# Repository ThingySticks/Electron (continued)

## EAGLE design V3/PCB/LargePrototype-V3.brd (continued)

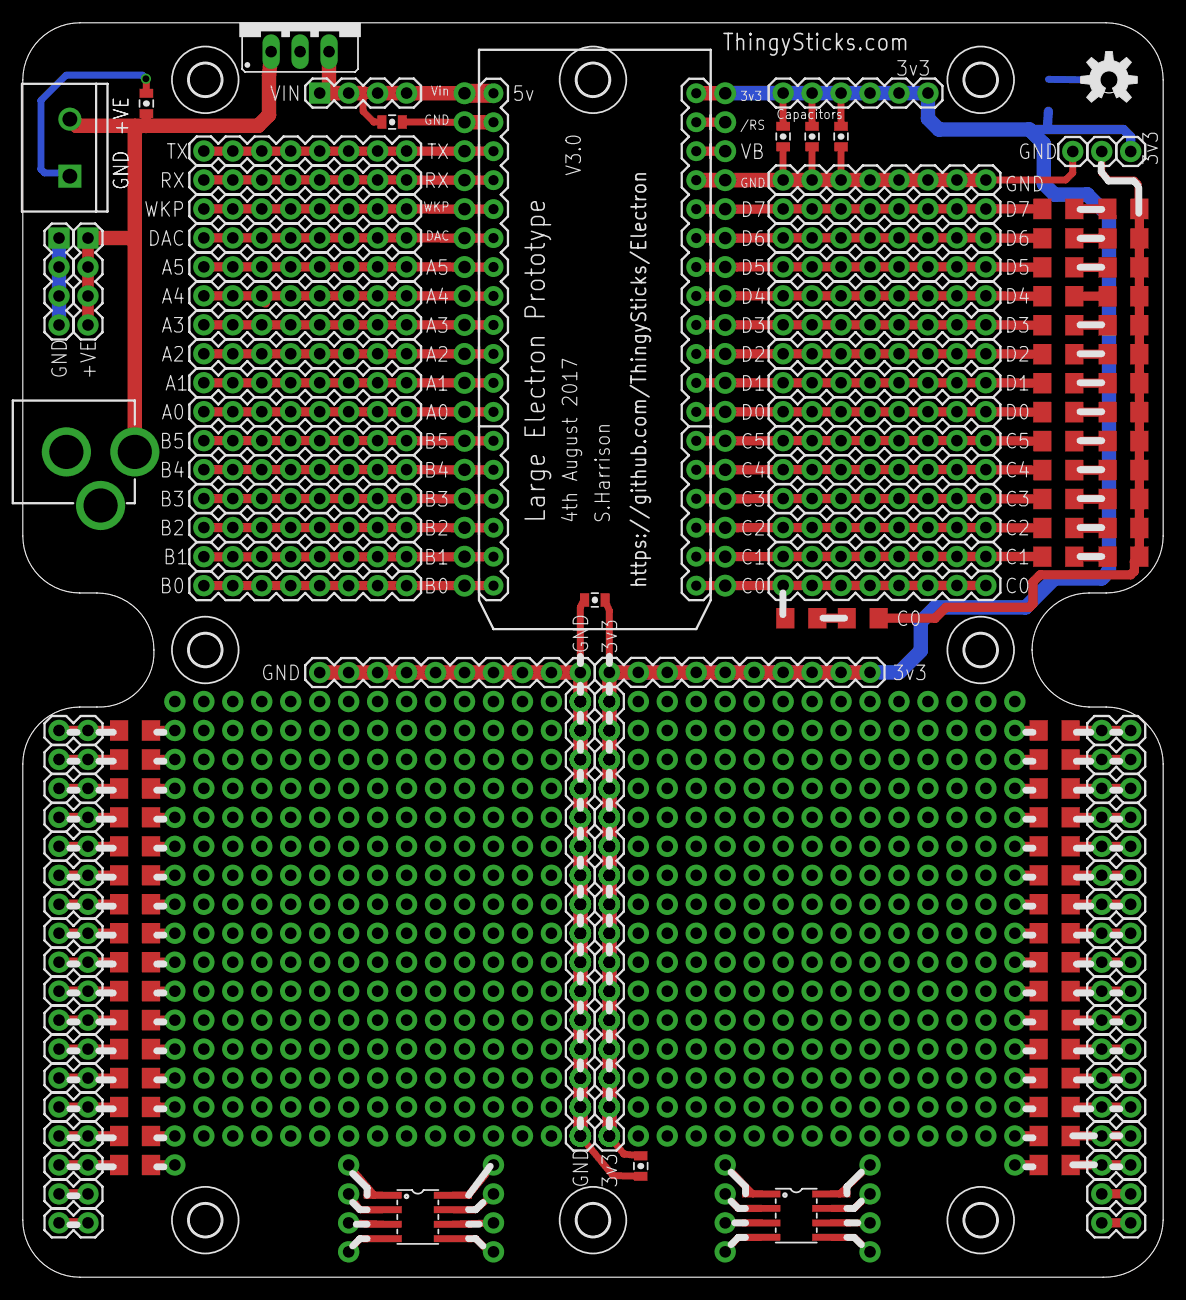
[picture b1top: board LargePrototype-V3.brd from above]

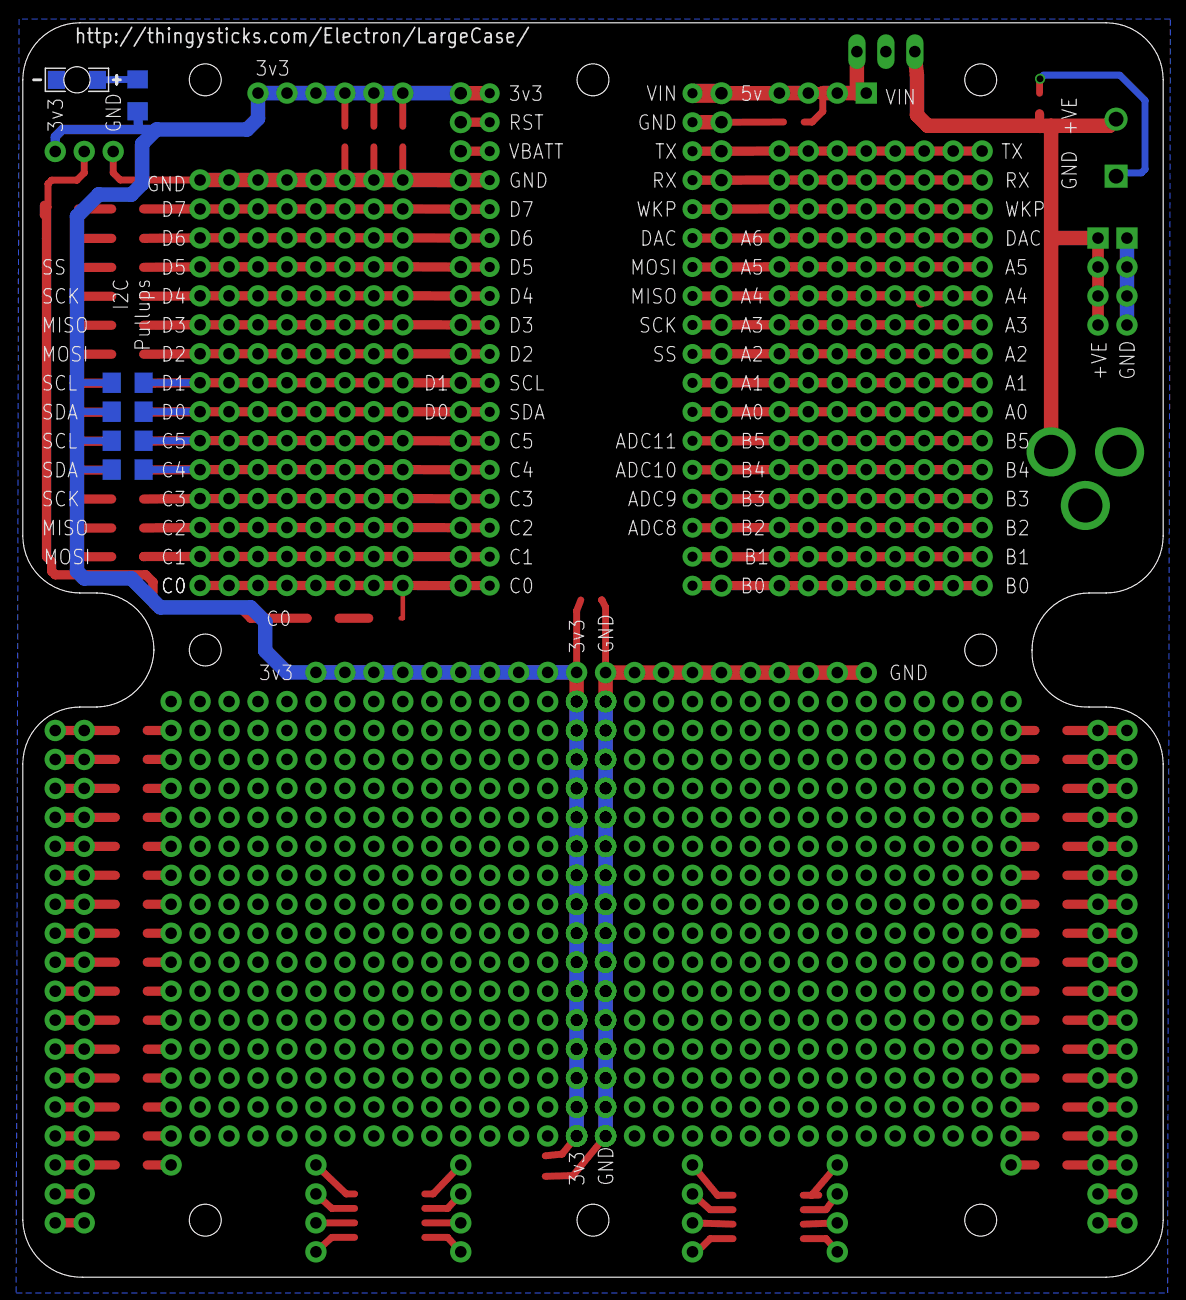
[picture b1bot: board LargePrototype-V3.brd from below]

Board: 2 copper layers, 100.0 x 110.0 mm, 205 parts (6 on the bottom side), 136 nets.

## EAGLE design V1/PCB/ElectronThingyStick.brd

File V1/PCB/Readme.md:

Electron Prototyping PCB.
=========================

Prototype board for Particle Electron.

Features:
---------

* USB power in via A Connector on left edge or B Connector on Electron. (Do not connect both at once).
* Pull-up and down 1206 pads on A0-A7 and B0-B7. Suitable for 1206 or 0805 components.
* LED/Resistor/Capacitor 1206 pads Right edge along with 10 x 2 header for off board connection (8 pins to 1206's + 2v2 & GND).
* 4 1206 pads top/bottom by end of Photon connected to pins to the right of the pad. Ideal of Capacitors, Resistor or LED.
* 3 Mounting holes to allow board to be mounted in case for final use.
* SOT-23 FET/Transistor under Photon with Gate/Base 1206 guard and pull down resistor options.

Mounting:
---------

Single hole middle PCB (at 14.5, 22)
Double holes end PCB (at 96,4 & 96,40)

Size:
-----
Length: 100mm
Width: 44mm

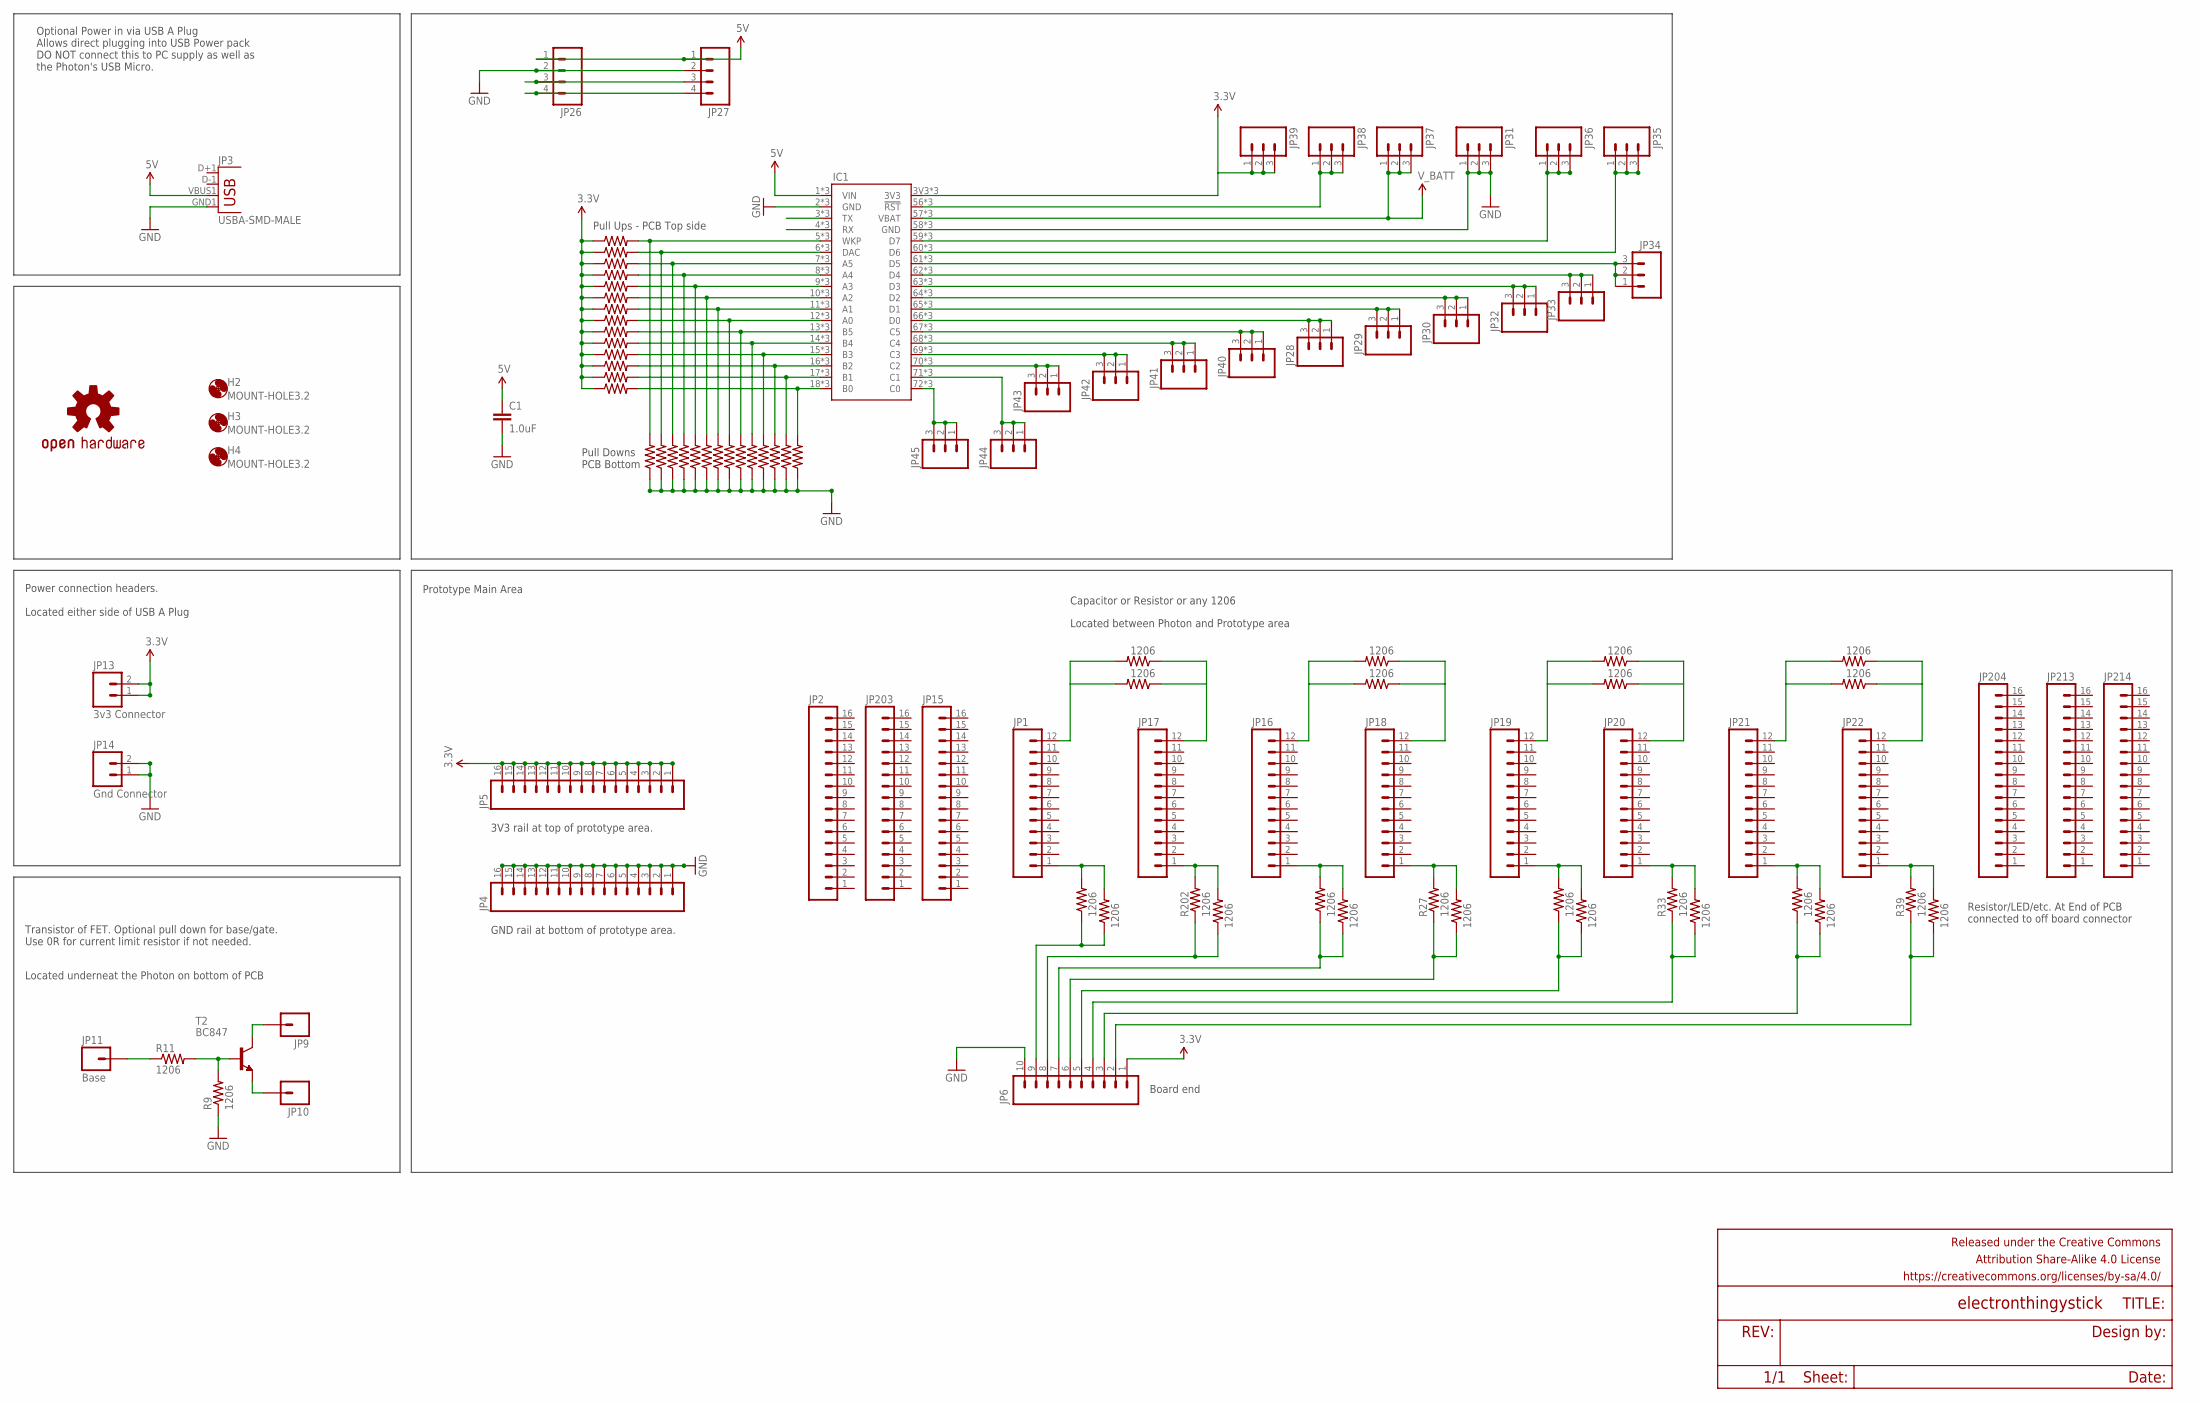
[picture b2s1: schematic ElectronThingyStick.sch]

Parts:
C1: 1.0uF; 0805-CAP
FRAME1: FRAME-LEDGER; CREATIVE_COMMONS
H2, H3, H4: MOUNT-HOLE3.2; 3,2
IC1: ELECTRONDUALROW; ELECTRON_DUAL-ROW
JP1, JP16, JP17, JP18, JP19, JP20, JP21, JP22: M12NO_SILK; 1X12_NO_SILK
JP2, JP15, JP203, JP204, JP213, JP214: M161X16_NO_SILK; 1X16_NO_SILK
JP3: USBA-SMD-MALE; USB-A-SMT-MALE
JP4, JP5: M16PTH; 1X16
JP6: M10NO_SILK_PTH_FEMALE; 1X10_NO_SILK
JP9, JP10: M01PTH; 1X01
JP11: Base; 1X01
JP13: 3v3 Connector; 1X02
JP14: Gnd Connector; 1X02
JP26, JP27: M041X04_NO_SILK; 1X04_NO_SILK
JP28, JP29, JP30, JP31, JP32, JP33, JP34, JP35, JP36, JP37, JP38, JP39, JP40, JP41, JP42, JP43, JP44, JP45: M03PTH; 1X03
LOGO1: OSHW-LOGOM; OSHW-LOGO-M
R1, R2, R3, R4, R5, R6, R7, R8, R9, R10, R11, R12, R13, R14, R15, R16, R17, R18, R19, R20, R21, R22, R23, R24, R25, R26, R27, R28, R29, R30, R31, R32, R33, R34, R35, R36, R37, R38, R39, R40, R41, R42, R43, R44, R45, R46, R47, R48, R49, R50, R51, R52, R201, R202: 1206
T2: BC847; SOT23

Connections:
3.3V: IC1.3V3, IC1.55 (3V3), IC1.91 (3V3), JP5.1, JP5.2, JP5.3, JP5.4, JP5.5, JP5.6, JP5.7, JP5.8, JP5.9, JP5.10, JP5.11, JP5.12, JP5.13, JP5.14, JP5.15, JP5.16, JP6.1, JP13.1, JP13.2, JP39.1, JP39.2, JP39.3, R1.1, R2.1, R3.1, R4.1, R5.1, R6.1, R7.1, R12.1, R15.1, R16.1, R17.1, R18.1, R45.1, R46.1
5V: C1.1, IC1.1 (VIN), IC1.37 (VIN), IC1.VIN, JP3.VBUS1 (VBUS), JP26.1, JP27.1
GND: C1.2, IC1.2 (GND), IC1.38 (GND), IC1.58 (GND), IC1.94 (GND), IC1.GND, IC1.GND@2 (GND), JP3.GND1 (GND), JP4.1, JP4.2, JP4.3, JP4.4, JP4.5, JP4.6, JP4.7, JP4.8, JP4.9, JP4.10, JP4.11, JP4.12, JP4.13, JP4.14, JP4.15, JP4.16, JP6.10, JP14.1, JP14.2, JP26.2, JP27.2, JP31.1, JP31.2, JP31.3, R8.1, R9.1, R10.1, R13.1, R14.1, R19.1, R20.1, R21.1, R22.1, R47.1, R48.1, R49.1, R50.1, R51.1, R52.1
unnamed: IC1.67 (C5), IC1.103 (C5), IC1.C5, JP40.1, JP40.2, JP40.3
unnamed: JP17.1, R26.2, R202.2
unnamed: JP1.1, R23.2, R201.2
unnamed: IC1.68 (C4), IC1.104 (C4), IC1.C4, JP41.1, JP41.2, JP41.3
unnamed: IC1.69 (C3), IC1.105 (C3), IC1.C3, JP42.1, JP42.2, JP42.3
unnamed: IC1.5 (WKP), IC1.41 (WKP), IC1.WKP, R8.2, R12.2
unnamed: IC1.6 (DAC), IC1.42 (DAC), IC1.DAC, R5.2, R10.2
unnamed: IC1.7 (A5), IC1.43 (A5), IC1.A5, R1.2, R13.2
unnamed: IC1.8 (A4), IC1.44 (A4), IC1.A4, R2.2, R14.2
unnamed: IC1.9 (A3), IC1.45 (A3), IC1.A3, R3.2, R19.2
unnamed: IC1.10 (A2), IC1.46 (A2), IC1.A2, R4.2, R20.2
unnamed: IC1.11 (A1), IC1.47 (A1), IC1.A1, R6.2, R21.2
unnamed: IC1.12 (A0), IC1.48 (A0), IC1.A0, R7.2, R22.2
unnamed: JP6.9, R23.1, R201.1
unnamed: IC1.70 (C2), IC1.106 (C2), IC1.C2, JP43.1, JP43.2, JP43.3
unnamed: IC1.61 (D5), IC1.97 (D5), IC1.D5, JP34.1, JP34.2, JP34.3
unnamed: IC1.62 (D4), IC1.98 (D4), IC1.D4, JP33.1, JP33.2, JP33.3
unnamed: IC1.63 (D3), IC1.99 (D3), IC1.D3, JP32.1, JP32.2, JP32.3
unnamed: IC1.64 (D2), IC1.100 (D2), IC1.D2, JP30.1, JP30.2, JP30.3
unnamed: IC1.65 (D1), IC1.101 (D1), IC1.D1, JP29.1, JP29.2, JP29.3
unnamed: IC1.66 (D0), IC1.102 (D0), IC1.D0, JP28.1, JP28.2, JP28.3
unnamed: IC1.13 (B5), IC1.49 (B5), IC1.B5, R15.2, R47.2
unnamed: JP1.12, R24.2, R25.2
unnamed: IC1.56 (!RST), IC1.92 (!RST), IC1.RST (!RST), JP38.1, JP38.2, JP38.3
unnamed: IC1.71 (C1), IC1.107 (C1), IC1.C1, JP44.1, JP44.2, JP44.3
unnamed: JP17.12, R24.1, R25.1
unnamed: IC1.72 (C0), IC1.108 (C0), IC1.C0, JP45.1, JP45.2, JP45.3
unnamed: JP6.8, R26.1, R202.1
unnamed: JP18.1, R27.2, R32.2
unnamed: JP16.1, R28.2, R29.2
unnamed: JP6.7, R28.1, R29.1
unnamed: IC1.14 (B4), IC1.50 (B4), IC1.B4, R16.2, R48.2
unnamed: JP16.12, R30.2, R31.2
unnamed: JP18.12, R30.1, R31.1
unnamed: IC1.15 (B3), IC1.51 (B3), IC1.B3, R17.2, R49.2
unnamed: JP6.6, R27.1, R32.1
unnamed: JP20.1, R33.2, R38.2
unnamed: IC1.59 (D7), IC1.95 (D7), IC1.D7, JP36.1, JP36.2, JP36.3
unnamed: IC1.60 (D6), IC1.96 (D6), IC1.D6, JP35.1, JP35.2, JP35.3
unnamed: JP19.1, R34.2, R35.2
unnamed: IC1.16 (B2), IC1.52 (B2), IC1.B2, R18.2, R50.2
unnamed: JP6.5, R34.1, R35.1
unnamed: IC1.17 (B1), IC1.53 (B1), IC1.B1, R45.2, R51.2
unnamed: IC1.18 (B0), IC1.54 (B0), IC1.B0, R46.2, R52.2
unnamed: JP19.12, R36.2, R37.2
unnamed: JP20.12, R36.1, R37.1
unnamed: JP6.4, R33.1, R38.1
unnamed: JP22.1, R39.2, R44.2
unnamed: JP11.1, R11.1
unnamed: R9.2, R11.2, T2.1 (B)
unnamed: JP9.1, T2.3 (C)
unnamed: JP10.1, T2.2 (E)
unnamed: JP21.1, R40.2, R41.2
unnamed: JP6.3, R40.1, R41.1
unnamed: JP21.12, R42.2, R43.2
unnamed: JP22.12, R42.1, R43.1
unnamed: JP6.2, R39.1, R44.1
RX: IC1.4 (RX), IC1.40 (RX), IC1.RX, JP26.4, JP27.4
TX: IC1.3 (TX), IC1.39 (TX), IC1.TX, JP26.3, JP27.3
V_BATT: IC1.57 (VBAT), IC1.93 (VBAT), IC1.VBAT, JP37.1, JP37.2, JP37.3

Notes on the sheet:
Prototype Main Area
Board end
Pull Ups - PCB Top side
Pull Downs PCB Bottom
Capacitor or Resistor or any 1206
Located between Photon and Prototype area
Resistor/LED/etc. At End of PCB connected to off board connector
Transistor of FET. Optional pull down for base/gate. Use 0R for current limit resistor if not needed.
Located underneat the Photon on bottom of PCB
Optional Power in via USB A Plug Allows direct plugging into USB Power pack DO NOT connect this to PC supply as well as the Photon's USB Micro.
Power connection headers. Located either side of USB A Plug
GND rail at bottom of prototype area.
3V3 rail at top of prototype area.

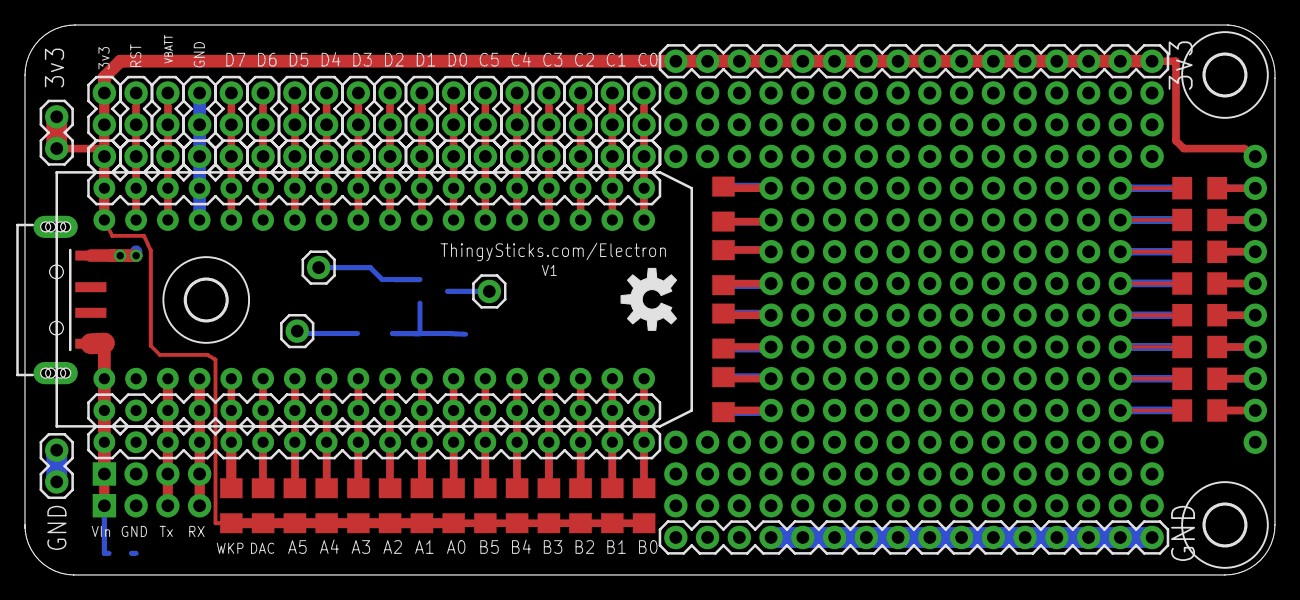
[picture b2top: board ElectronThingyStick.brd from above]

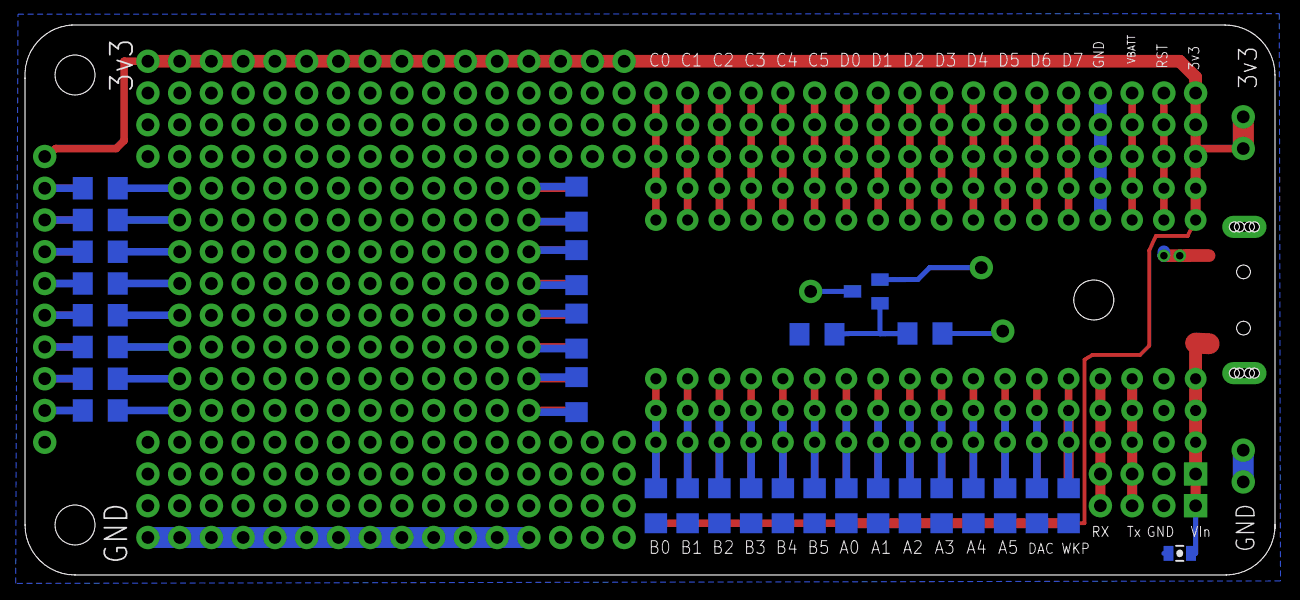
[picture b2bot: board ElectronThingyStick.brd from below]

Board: 2 copper layers, 100.0 x 44.0 mm, 105 parts (30 on the bottom side), 63 nets.

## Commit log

2016-11-18 Initial version
2016-11-20 Added DirtyPCB images and updated readme for mounting hole positions.
2017-01-04 Corrected electron name and minor tidyup.
    Added pdfs of the PCB.
    Added BOM to list the parts
2017-01-04 Fixed json validation issues for BOM.
2017-05-05 Start of large electron prototype PCB
2017-05-05 Minor fixes for location of silk screen.
    Added pdf's and images of pcb/schematic.
    Added to DirtyPCBs order.
2017-05-29 Relabelled large electron prototype as V2 to match the folder.
    Improved silk screen
    Removed jumper links for electron pins so they are connected through
    Added a couple more capacitor places.
    Added 3v3 and GND links to lower half board edge
2017-05-29 Updated PDF's to V2
    Added images for V2 (keeping originals)
2017-05-29 Added 3D Printable footprint.
2017-06-14 Changed aerial options to slot / pad.
    Added variables for screw hole size to allow for future self-tapper vs threaded insert option.
    Updated build.bat for base to use new settings for aerial option.
    Rebuilt.
2017-06-14 Version of the base with mounts for the Asset Tracker
2017-06-14 Improved comments for use with Thiniverse customizer.
    Fixed aerial slot/pad height to be inline with the base thinckness.
2017-08-03 Added BOM.
2017-08-03 Renamed electron & added pictures.
2017-11-26 Added V3 PCB designed for Takachi IP67 enclosure.
2017-11-27 Added Tindie Link
